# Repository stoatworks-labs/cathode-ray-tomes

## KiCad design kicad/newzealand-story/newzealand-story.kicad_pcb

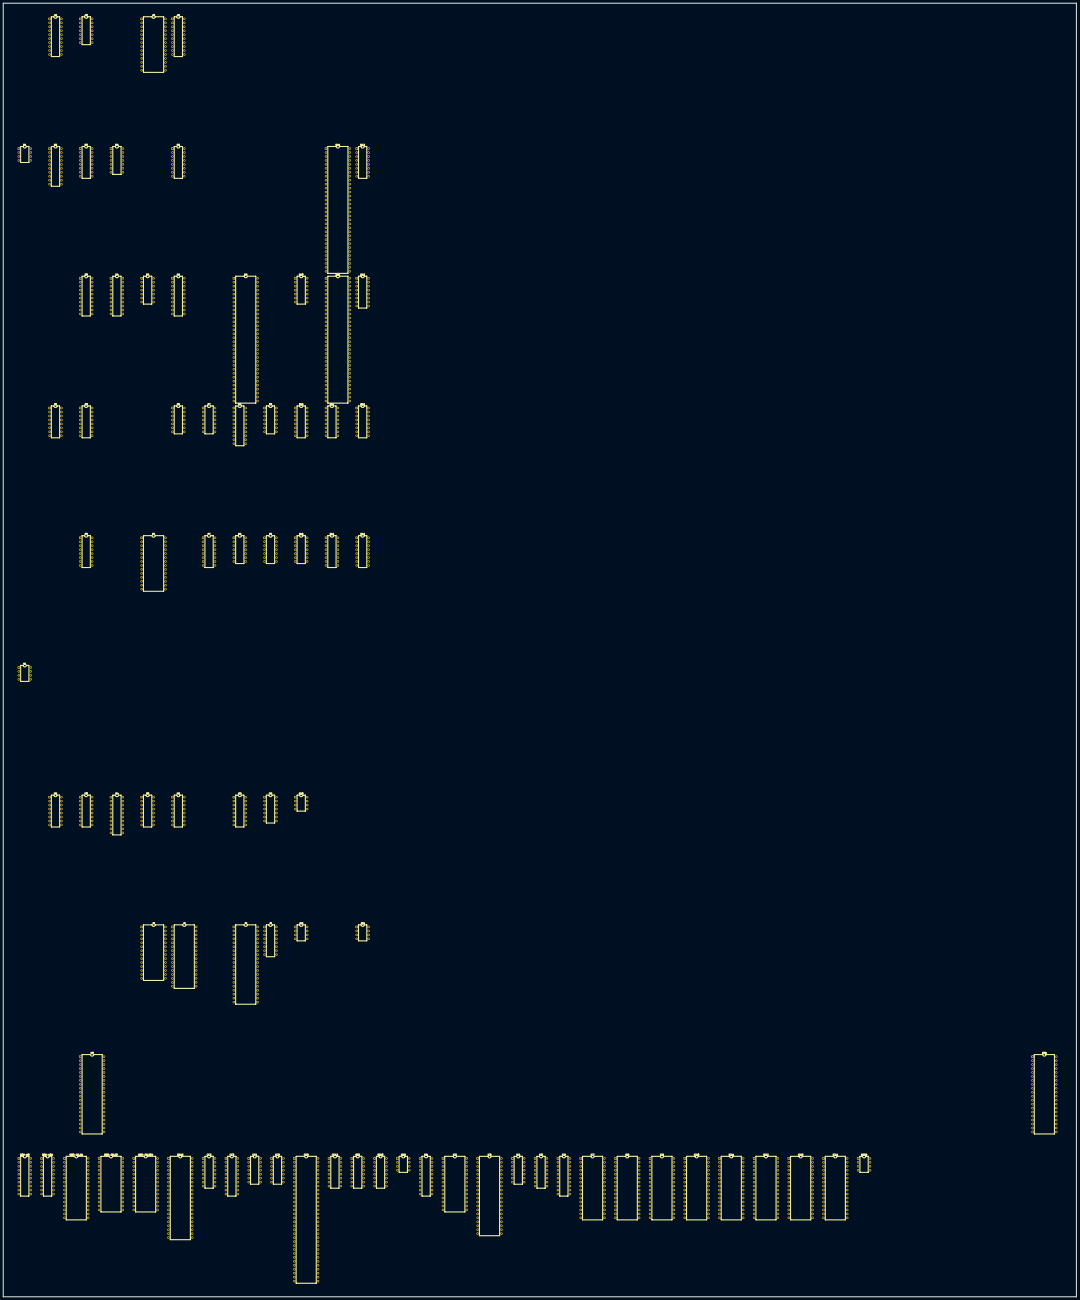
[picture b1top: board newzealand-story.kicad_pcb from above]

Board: 2 copper layers, 688.3 x 829.6 mm, 83 parts (0 on the bottom side), 406 nets, no tracks yet.

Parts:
A2: 74HC245; DIP-20_W7.62mm
A3: 74LS107; DIP-14_W7.62mm
A5: 6264SL; DIP-28_W15.24mm
A6: 74HC273; DIP-20_W7.62mm
B1: R0-012; DIP-8_W7.62mm
B2: 74HC245; DIP-20_W7.62mm
B3: 74F157; DIP-16_W7.62mm
B4: 74F32; DIP-14_W7.62mm
B6: 74HC174; DIP-16_W7.62mm
B06-13, B06-101: PAL16L8’; DIP-20_W7.62mm
B11: X1-006; DIP-64_W15.24mm
B12: X2-004; DIP-16_W7.62mm
B53-24.U1: 27C010; DIP-32_W15.24mm
B53-25.U3, B53-26.U34: 27512; DIP-28_W15.24mm
BB12: X1-007; DIP-42_W15.24mm
CC2: 74HC174; DIP-16_W7.62mm
CC3: 74HC245; DIP-20_W7.62mm
CC4: 74LS32; DIP-14_W7.62mm
CC5: 74F08; DIP-14_W7.62mm
CC8: YM3909; DIP-64_W15.24mm
CC12: X2-004; DIP-16_W7.62mm
D3, D4: 74HC245; DIP-20_W7.62mm
D5: 74LS32; DIP-14_W7.62mm
D6: 74HC374; DIP-20_W7.62mm
D8: YM3906; DIP-64_W15.24mm
D10: 74LS04; DIP-14_W7.62mm
D11: X1-004; DIP-64_W15.24mm
D12: X2-004; DIP-16_W7.62mm
E2, E3: 74LS157; DIP-16_W7.62mm
E6: 74F04; DIP-14_W7.62mm
E7: 74LS08; DIP-14_W7.62mm
E8: 74LS244_Split; DIP-20_W7.62mm
E9: 74LS74; DIP-14_W7.62mm
E10: 74LS139; DIP-16_W7.62mm
E11: 4050; DIP-16_W7.62mm
E12: X2-004; DIP-16_W7.62mm
EE8: 74LS157; DIP-16_W7.62mm
EE10: 74HC161; DIP-16_W7.62mm
F3, F7: 74LS157; DIP-16_W7.62mm
F5: uPD4464; DIP-28_W15.24mm
F8: 74LS74; DIP-14_W7.62mm
F9: 74LS32; DIP-14_W7.62mm
F10: 74HC14; DIP-14_W7.62mm
F11: 74HC161; DIP-16_W7.62mm
F12: TD62064; DIP-16_W7.62mm
G1: R0-012; DIP-8_W7.62mm
H2, H3: 74HC257; DIP-16_W7.62mm
H4: 74HC374; DIP-20_W7.62mm
H5: 74HC174; DIP-16_W7.62mm
H6: 74LS139; DIP-16_W7.62mm
H8: 74LS253; DIP-16_W7.62mm
H9: 74LS20; DIP-14_W7.62mm
H10: RC4558; DIP-8_W7.62mm
HH9: YM3014; DIP-8_W7.62mm
IC1: 74F245; DIP-20_W7.62mm
IC2: SRM20256; DIP-28_W15.24mm
IC3: Z80CPU; DIP-40_W15.24mm
IC4: 74HC08; DIP-14_W7.62mm
IC5: 74LS174; DIP-16_W7.62mm
IC6: PAL16L8’; DIP-20_W7.62mm
IC7, IC8, IC9, IC10, IC11, IC12, IC13, IC14: 27C010; DIP-32_W15.24mm
J5: HM65256BLP-12; DIP-28_W15.24mm
J6: 27C010; DIP-32_W15.24mm
J8: YM2203; DIP-40_W15.24mm
J9: HA17408; DIP-16_W7.62mm
J10: RC4558; DIP-8_W7.62mm
J12: MB3730; DIP-8_W7.62mm
R999: R0-012; DIP-8_W7.62mm
U3, U34: Z80CPU; DIP-40_W15.24mm

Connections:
+5V: H10.8, J9.13, J10.8
+12V: E11.1, F12.1, F12.8, J12.7
-5V: H10.4, J9.3
/CPU/H2B: B4.10, E7.4, E8.14, E9.12
/CPU/H4B: A2.19, B2.19, D5.12, E7.5, E8.12
/CPU/MCK6M: E9.3, IC4.9
/CPU/SA0: B11.48, B11.56, B53-25.U3.10, D11.37, EE8.2, H2.1, H3.1, U3.30
/CPU/SA1: B11.49, B11.57, B53-25.U3.9, E3.14, E10.2, F9.12, U3.31
/CPU/SA2: B11.50, B11.58, B53-25.U3.8, E3.11, F9.9, U3.32
/CPU/SA3: B11.51, B11.59, B53-25.U3.7, E3.5, U3.33
/CPU/SA4: B11.52, B11.60, B53-25.U3.6, E3.2, U3.34
/CPU/SA5: B11.53, B11.61, B53-25.U3.5, F3.14, U3.35
/CPU/SA6: B11.54, B11.62, B53-25.U3.4, F3.11, U3.36
/CPU/SA7: B11.55, B11.63, B53-25.U3.3, F3.5, U3.37
/CPU/SA8: B53-25.U3.25, F3.2, U3.38
/CPU/SA9: B53-25.U3.24, E2.14, U3.39
/CPU/SA10: B53-25.U3.21, E2.11, U3.40
/CPU/SA11: B06-13.5, B53-25.U3.23, E2.5, U3.1
/CPU/SA12: B06-13.4, B53-25.U3.2, E2.2, U3.2
/CPU/SA13: B06-13.3, U3.3
/CPU/SA14: B06-13.2, U3.4
/CPU/SA15: B06-13.1, B53-25.U3.1, U3.5
/CPU/SBSWD0: B06-13.11, D11.28, H5.15
/CPU/SBSWD1: B06-13.9, D11.29, H5.12
/CPU/SBSWD3: D11.31, H5.7
/CPU/SHA0: EE8.4, F5.10
/CPU/SHA1: E3.12, F5.9
/CPU/SHA2: E3.9, F5.8
/CPU/SHA3: E3.7, F5.7
/CPU/SHA4: E3.4, F5.6
/CPU/SHA5: F3.12, F5.5
/CPU/SHA6: F3.9, F5.4
/CPU/SHA7: F3.7, F5.3
/CPU/SHA8: F3.4, F5.25
/CPU/SHA9: E2.12, F5.24
/CPU/SHA10: E2.9, F5.21
/CPU/SHA11: E2.7, F5.23
/CPU/SHA12: E2.4, F5.2
/CPU/SHD0: D3.11, D4.11, F5.11
/CPU/SHD1: D3.12, D4.12, F5.12
/CPU/SHD2: D3.13, D4.13, F5.13
/CPU/SHD3: D3.14, D4.14, F5.15
/CPU/SHD4: D3.15, D4.15, F5.16
/CPU/SHD5: D3.16, D4.16, F5.17
/CPU/SHD6: D3.17, D4.17, F5.18
/CPU/SHD7: D3.18, D4.18, F5.19
/CPU/SRA13: B06-13.18, B53-25.U3.26
/CPU/SRA14: B06-13.19, B53-25.U3.27
/CPU/~BGTRNSP: B06-101.14, CC8.2
/CPU/~BNKSW: B06-101.15, CC2.9, D10.13
/CPU/~DIPSND: B06-13.15, F9.10, F9.13
/CPU/~H4: D6.1, E6.8, E7.2
/CPU/~MRD: CC3.1, D3.1, D8.2, E6.1, EE8.6, IC1.1, IC2.22, IC3.21, IC6.9
/CPU/~MRFSH: B06-101.9, E10.14, IC3.28
/CPU/~MSHRAMEN: CC4.6, CC5.13, D3.19, D5.10, E6.11
/CPU/~MSHRAMRQ: B06-101.18, CC4.2, CC4.4
/CPU/~MWR: B06-101.11, D5.9, IC2.27, IC3.22, IC6.8
/CPU/~OBJORVRAMEN: B06-101.19, CC4.13, D5.2, D5.13
/CPU/~OBJRAMCS: A5.20, E7.3
/CPU/~OE: EE8.7, F5.22
/CPU/~PALEN: B06-13.17, B11.45
/CPU/~RDINPUTS: B06-13.16, E10.1
/CPU/~SBNKSW: B06-13.14, H5.9
/CPU/~SMREQ: B06-13.7, U3.19
/CPU/~SRD: B11.44, D4.1, EE8.5, U3.21
/CPU/~SRFSH: B06-13.8, U3.28
/CPU/~SROMCS: B06-13.12, B53-25.U3.22
/CPU/~SRST: CC2.5, H5.1, J8.24, U3.26, U34.26
/CPU/~SSHRAMEN: CC4.1, CC4.8, CC4.12, CC5.12, D4.19, E2.1, E3.1, E6.13, EE8.1, F3.1
/CPU/~SSHRAMRQ: B06-13.13, CC4.10, D5.5
/CPU/~SWAIT: D5.6, U3.24
/CPU/~SWR: B06-13.6, B11.47, U3.22
/CPU/~VRAMWR: B06-101.13, D8.3
/Graphics/12M: CC8.3, D8.62
/Graphics/B1: B1.2, BB12.1
/Graphics/B2: B1.3, BB12.2
/Graphics/B3: B1.4, BB12.3
/Graphics/B4: B1.5, BB12.4
/Graphics/B5: B1.6, BB12.5
/Graphics/B6: B1.7, BB12.6
/Graphics/G1: BB12.7, G1.2
/Graphics/G2: BB12.8, G1.3
/Graphics/G3: BB12.9, G1.4
/Graphics/G4: BB12.11, G1.5
/Graphics/G5: BB12.12, G1.6
/Graphics/G6: BB12.13, G1.7
/Graphics/GA0: D8.35, IC7.12, IC8.12, IC9.12, IC10.12, IC11.12, IC12.12, IC13.12, IC14.12
/Graphics/GA1: D8.36, IC7.11, IC8.11, IC9.11, IC10.11, IC11.11, IC12.11, IC13.11, IC14.11
/Graphics/GA2: D8.37, IC7.10, IC8.10, IC9.10, IC10.10, IC11.10, IC12.10, IC13.10, IC14.10
/Graphics/GA4: D8.38, IC7.8, IC8.8, IC9.8, IC10.8, IC11.8, IC12.8, IC13.8, IC14.8
/Graphics/GA5: A6.19, IC7.7, IC8.7, IC9.7, IC10.7, IC11.7, IC12.7, IC13.7, IC14.7
/Graphics/GA6: A6.16, IC7.6, IC8.6, IC9.6, IC10.6, IC11.6, IC12.6, IC13.6, IC14.6
/Graphics/GA7: A6.15, IC7.5, IC8.5, IC9.5, IC10.5, IC11.5, IC12.5, IC13.5, IC14.5
/Graphics/GA8: A6.12, IC7.27, IC8.27, IC9.27, IC10.27, IC11.27, IC12.27, IC13.27, IC14.27
/Graphics/GA9: A6.9, IC7.26, IC8.26, IC9.26, IC10.26, IC11.26, IC12.26, IC13.26, IC14.26
/Graphics/GA10: A6.6, IC7.23, IC8.23, IC9.23, IC10.23, IC11.23, IC12.23, IC13.23, IC14.23
/Graphics/GA11: A6.5, IC7.25, IC8.25, IC9.25, IC10.25, IC11.25, IC12.25, IC13.25, IC14.25
/Graphics/GA12: A6.2, IC7.4, IC8.4, IC9.4, IC10.4, IC11.4, IC12.4, IC13.4, IC14.4
/Graphics/GA13: B6.15, IC7.28, IC8.28, IC9.28, IC10.28, IC11.28, IC12.28, IC13.28, IC14.28
/Graphics/GA14: B6.12, IC7.29, IC8.29, IC9.29, IC10.29, IC11.29, IC12.29, IC13.29, IC14.29
/Graphics/GA15: B6.10, IC7.3, IC8.3, IC9.3, IC10.3, IC11.3, IC12.3, IC13.3, IC14.3
/Graphics/GA16: B6.7, IC7.2, IC8.2, IC9.2, IC10.2, IC11.2, IC12.2, IC13.2, IC14.2
/Graphics/GDA0: CC8.56, IC7.13, IC8.13
/Graphics/GDA1: CC8.57, IC7.14, IC8.14
/Graphics/GDA2: CC8.58, IC7.15, IC8.15
/Graphics/GDA3: CC8.59, IC7.17, IC8.17
/Graphics/GDA4: CC8.60, IC7.18, IC8.18
/Graphics/GDA5: CC8.61, IC7.19, IC8.19
/Graphics/GDA6: CC8.62, IC7.20, IC8.20
/Graphics/GDA7: CC8.63, IC7.21, IC8.21
/Graphics/GDB0: CC8.48, IC9.13, IC10.13
/Graphics/GDB1: CC8.49, IC9.14, IC10.14
/Graphics/GDB2: CC8.50, IC9.15, IC10.15
/Graphics/GDB3: CC8.51, IC9.17, IC10.17
/Graphics/GDB4: CC8.52, IC9.18, IC10.18
/Graphics/GDB5: CC8.53, IC9.19, IC10.19
/Graphics/GDB6: CC8.54, IC9.20, IC10.20
/Graphics/GDB7: CC8.55, IC9.21, IC10.21
/Graphics/GDC0: CC8.40, IC11.13, IC13.13
/Graphics/GDC1: CC8.41, IC11.14, IC13.14
/Graphics/GDC2: CC8.42, IC11.15, IC13.15
/Graphics/GDC3: CC8.43, IC11.17, IC13.17
/Graphics/GDC4: CC8.44, IC11.18, IC13.18
/Graphics/GDC5: CC8.45, IC11.19, IC13.19
/Graphics/GDC6: CC8.46, IC11.20, IC13.20
/Graphics/GDC7: CC8.47, IC11.21, IC13.21
/Graphics/GDD0: CC8.30, IC12.13, IC14.13
/Graphics/GDD1: CC8.31, IC12.14, IC14.14
/Graphics/GDD2: CC8.34, IC12.15, IC14.15
/Graphics/GDD3: CC8.35, IC12.17, IC14.17
/Graphics/GDD4: CC8.36, IC12.18, IC14.18
/Graphics/GDD5: CC8.37, IC12.19, IC14.19
/Graphics/GDD6: CC8.38, IC12.20, IC14.20
/Graphics/GDD7: CC8.39, IC12.21, IC14.21
/Graphics/H: D8.40, E8.4
/Graphics/H2: D8.41, E8.6
/Graphics/H2SYNC: B4.8, D6.11, E6.3
/Graphics/H4: D8.42, E6.9, E8.8, H8.14
/Graphics/H8: A6.11, B6.9, D8.43, EE10.2
/Graphics/H8R: D8.34, IC7.9, IC8.9, IC9.9, IC10.9, IC11.9, IC12.9, IC13.9, IC14.9
/Graphics/HX: D8.39, E8.2
/Graphics/MAB11: B2.16, D8.27
/Graphics/OBJRD: B4.13, D8.30
/Graphics/R1: BB12.14, R999.2
/Graphics/R2: BB12.15, R999.3
/Graphics/R3: BB12.16, R999.4
/Graphics/R4: BB12.17, R999.5
/Graphics/R5: BB12.18, R999.6
/Graphics/R6: BB12.19, R999.7
/Graphics/VA0: A2.13, A5.10, D8.15
/Graphics/VA1: A2.14, A5.9, D8.16
/Graphics/VA2: A2.15, A5.8, D8.17
/Graphics/VA3: A2.16, A5.7, D8.18
/Graphics/VA4: A2.17, A5.6, D8.19
/Graphics/VA5: A2.18, A5.5, D8.20
/Graphics/VA6: A5.4, B2.11, D8.21
/Graphics/VA7: A5.3, B2.12, D8.22
/Graphics/VA8: A5.25, B2.13, D8.23
/Graphics/VA9: A5.24, B2.14, D8.24
/Graphics/VA10: A5.21, B2.15, D8.25
/Graphics/VA11: A5.23, D8.28
/Graphics/VA12: A5.2, H8.7
/Graphics/VD0: A5.11, A6.18, CC3.11, D6.18, D8.14
/Graphics/VD1: A5.12, A6.17, CC3.12, D6.17, D8.13
/Graphics/VD2: A5.13, A6.14, CC3.13, D6.14, D8.12
/Graphics/VD3: A5.15, A6.13, CC3.14, D6.13, D8.11
/Graphics/VD4: A5.16, A6.8, CC3.15, D6.8, D8.10
/Graphics/VD5: A5.17, A6.7, CC3.16, D6.7, D8.9
/Graphics/VD6: A5.18, A6.4, B2.3, CC3.17, D6.4, D8.8
/Graphics/VD7: A5.19, A6.3, B2.2, CC3.18, D6.3, D8.7
/Graphics/VDB0: B6.14, D6.19, D8.4
/Graphics/VDB1: B6.13, D6.16
/Graphics/VDB2: A2.12, B6.11, CC8.10, D6.15
/Graphics/VDB3: B6.6, CC8.9, D6.12
/Graphics/VDB4: B6.4, CC8.8, D6.9
/Graphics/VDB5: B6.3, CC8.7, D6.6
/Graphics/VDB6: B2.17, CC8.6, D6.5, D8.59
/Graphics/VDB7: B2.18, CC8.5, D6.2, D8.60
/Graphics/~GROMEN: B6.5, IC6.7, IC7.24, IC9.24, IC11.24, IC12.24
/Graphics/~HBLK2: D8.57, D10.9
/Graphics/~HBLK: D8.55, F10.1
/Graphics/~VBLK: A3.9, A3.12, BB12.24, D8.58
/Graphics/~VSYNC: BB12.23, D8.56
/IO/1P_BTN_1_B: D11.5, E12.12
/IO/1P_BTN_2_B: D11.4, E12.13
/IO/1P_BTN_3_B: D11.3, E12.14
/IO/1P_DOWN_B: D11.6, E12.11
/IO/1P_LEFT_B: D11.9, D12.14
/IO/1P_RIGHT_B: D11.8, D12.15
/IO/1P_START_B: D11.2, E12.15
/IO/1P_UP_B: D11.7, E12.10
/IO/2P_BTN_1_B: D11.13, D12.10
/IO/2P_BTN_2_B: D11.12, D12.11
/IO/2P_BTN_3_B: D11.11, D12.12
/IO/2P_DOWN_B: CC12.15, D11.14
/IO/2P_LEFT_B: CC12.12, D11.17
/IO/2P_RIGHT_B: CC12.13, D11.16
/IO/2P_START_B: D11.10, D12.13
/IO/2P_UP_B: CC12.14, D11.15
/IO/COIN_1_B: B12.14, D11.21
/IO/COIN_2_B: B12.15, D11.20
/IO/COIN_CNT_1_B: D11.25, F12.11
/IO/COIN_CNT_2_B: D11.24, F12.6
/IO/COIN_LOCK_1_B: D11.22, F12.14
/IO/COIN_LOCK_2_B: D11.23, F12.3
/IO/SD0: B53-25.U3.11, D4.9, D11.34, D11.44, H3.4, H4.18, H5.14, U3.14
/IO/SD1: B53-25.U3.12, D4.8, D11.35, D11.45, H3.7, H4.17, H5.13, U3.15
/IO/SD2: B53-25.U3.13, D4.7, D11.46, H3.9, H4.14, H5.11, U3.12
/IO/SD3: B53-25.U3.15, D4.6, D11.47, H3.12, H4.13, H5.6, U3.8
/IO/SD4: B53-25.U3.16, D4.5, D11.32, D11.48, H2.4, H4.8, H5.4, U3.7
/IO/SD5: B53-25.U3.17, D4.4, D11.33, D11.49, H2.7, H4.7, H5.3, U3.9
/IO/SD6: B53-25.U3.18, D4.3, D11.50, H2.9, H4.4, U3.10
/IO/SD7: B53-25.U3.19, D4.2, D11.51, H2.12, H4.3, U3.13
/IO/SERVICE_B: CC12.10, D11.19
/IO/TILT_B: CC12.11, D11.18
/Misc/HB: E8.3, F8.11
/Sound/DA0: J8.26, J9.12
/Sound/DA1: J8.27, J9.11
/Sound/DA2: J8.28, J9.10
/Sound/DA3: J8.29, J9.9
/Sound/DA4: J8.30, J9.8
/Sound/DA5: J8.31, J9.7
/Sound/DA6: J8.32, J9.6
/Sound/DA7: J8.33, J9.5
/Sound/ROMA14: B53-26.U34.27, F7.12, J6.29
/Sound/ROMA15: B53-26.U34.1, F7.7, J6.3
/Sound/S2A0: B53-26.U34.10, J5.10, J6.12, J8.37, U34.30
/Sound/S2A1: B53-26.U34.9, H6.14, J5.9, J6.11, U34.31
/Sound/S2A2: B53-26.U34.8, J5.8, J6.10, U34.32
/Sound/S2A3: B53-26.U34.7, J5.7, J6.9, U34.33
/Sound/S2A4: B53-26.U34.6, J5.6, J6.8, U34.34
/Sound/S2A5: B53-26.U34.5, J5.5, J6.7, U34.35
/Sound/S2A6: B53-26.U34.4, J5.4, J6.6, U34.36
/Sound/S2A7: B53-26.U34.3, J5.3, J6.5, U34.37
/Sound/S2A8: B53-26.U34.25, J5.25, J6.27, U34.38
/Sound/S2A9: B53-26.U34.24, J5.24, J6.26, U34.39
/Sound/S2A10: B53-26.U34.21, J5.21, J6.23, U34.40
/Sound/S2A11: B53-26.U34.23, J5.23, J6.25, U34.1
/Sound/S2A12: B53-26.U34.2, J5.2, J6.4, U34.2
/Sound/S2A13: B53-26.U34.26, J6.28, U34.3
/Sound/S2A14: F7.14, H6.2, U34.4
/Sound/S2A15: F7.1, H6.3, U34.5
/Sound/S2D0: B53-26.U34.11, H4.19, J5.11, J6.13, J8.40, U34.14
/Sound/S2D1: B53-26.U34.12, H4.16, J5.12, J6.14, J8.2, U34.15
/Sound/S2D2: B53-26.U34.13, H4.15, J5.13, J6.15, J8.3, U34.12
/Sound/S2D3: B53-26.U34.15, H4.12, J5.15, J6.17, J8.4, U34.8
/Sound/S2D4: B53-26.U34.16, H4.9, J5.16, J6.18, J8.5, U34.7
/Sound/S2D5: B53-26.U34.17, H4.6, J5.17, J6.19, J8.6, U34.9
/Sound/S2D6: B53-26.U34.18, H4.5, J5.18, J6.20, J8.7, U34.10
/Sound/S2D7: B53-26.U34.19, H4.2, J5.19, J6.21, J8.8, U34.13
/Sound/YMROMA14: F7.13, J8.16
/Sound/YMROMA15: F7.6, J8.15
/Sound/~ROMCS2: B53-26.U34.20, J6.22
/Sound/~ROMOE2: B53-26.U34.22, J6.24
/Sound/~S2INT: F8.6, U34.16
/Sound/~S2IORQ: H6.15, U34.20
/Sound/~S2M1: D10.11, H6.13, U34.27
/Sound/~S2MREQ: F7.11, H6.1, U34.19
/Sound/~S2RAMCS: H6.7, J5.20
/Sound/~S2RD: J5.22, J8.36, U34.21
/Sound/~S2ROMHCS: F7.10, H6.6
/Sound/~S2WR: J5.27, J8.35, U34.22
/Sound/~YMCS: H6.10, J8.34
/Sound/~YMIRQ: J8.25, U34.17
/Sound/~YMROMOE: F7.3, J8.14
/Sub PCB/MA0: A2.7, B53-24.U1.12, CC3.9, EE8.3, IC2.10, IC3.30
/Sub PCB/MA1: A2.6, B53-24.U1.11, CC3.8, E3.13, IC2.9, IC3.31
/Sub PCB/MA2: A2.5, B53-24.U1.10, CC3.7, E3.10, IC2.8, IC3.32
/Sub PCB/MA3: A2.4, B53-24.U1.9, CC3.6, E3.6, IC2.7, IC3.33
/Sub PCB/MA4: A2.3, B53-24.U1.8, CC3.5, E3.3, IC2.6, IC3.34
/Sub PCB/MA5: A2.2, B53-24.U1.7, CC3.4, F3.13, IC2.5, IC3.35
/Sub PCB/MA6: B2.9, B53-24.U1.6, CC3.3, F3.10, IC2.4, IC3.36
/Sub PCB/MA7: B2.8, B53-24.U1.5, CC3.2, F3.6, IC2.3, IC3.37
/Sub PCB/MA8: B2.7, B53-24.U1.27, F3.3, IC2.25, IC3.38
/Sub PCB/MA9: B2.6, B06-101.7, B53-24.U1.26, E2.13, IC2.24, IC3.39, IC6.18
/Sub PCB/MA10: B2.5, B06-101.6, B53-24.U1.23, E2.10, IC2.21, IC3.40, IC6.1
/Sub PCB/MA11: B2.4, B06-101.5, B53-24.U1.25, D8.26, E2.6, IC2.23, IC3.1, IC6.2
/Sub PCB/MA12: B06-101.4, B53-24.U1.4, E2.3, IC2.2, IC3.2, IC6.3
/Sub PCB/MA13: B06-101.3, B53-24.U1.28, D10.1, IC2.26, IC3.3, IC6.4
/Sub PCB/MA14: B3.10, B4.2, B06-101.2, H9.2, IC3.4, IC6.5
/Sub PCB/MA15: B06-101.1, CC5.2, D10.5, H9.1, IC3.5, IC6.6
/Sub PCB/MBD0: B53-24.U1.13, CC2.14, D3.9, IC1.18
/Sub PCB/MBD1: B53-24.U1.14, CC2.13, D3.8, IC1.17
/Sub PCB/MBD2: B53-24.U1.15, CC2.11, D3.7, IC1.16
/Sub PCB/MBD3: B53-24.U1.17, CC2.6, D3.6, IC1.15
/Sub PCB/MBD4: B53-24.U1.18, CC2.4, D3.5, IC1.14
/Sub PCB/MBD5: B53-24.U1.19, CC2.3, D3.4, IC1.13
/Sub PCB/MBD6: B53-24.U1.20, D3.3, IC1.12
/Sub PCB/MBD7: B53-24.U1.21, D3.2, IC1.11
/Sub PCB/MD0: IC1.2, IC2.11, IC3.14, IC5.3
/Sub PCB/MD1: IC1.3, IC2.12, IC3.15, IC5.4
/Sub PCB/MD2: IC1.4, IC2.13, IC3.12, IC5.6
/Sub PCB/MD3: IC1.5, IC2.15, IC3.8, IC5.11
/Sub PCB/MD4: IC1.6, IC2.16, IC3.7, IC5.13
/Sub PCB/MD5: IC1.7, IC2.17, IC3.9, IC5.14
/Sub PCB/MD6: IC1.8, IC2.18, IC3.10
/Sub PCB/MD7: IC1.9, IC2.19, IC3.13
/Sub PCB/MDC0: IC2.1, IC5.2, IC6.17
/Sub PCB/MDC1: IC5.5, IC6.16
/Sub PCB/MDC2: IC5.7, IC6.15
/Sub PCB/~GROMENB: IC6.14, IC8.24, IC10.24, IC13.24, IC14.24
/Sub PCB/~MINT: A3.6, IC3.16
/Sub PCB/~MIORQ: A3.10, IC3.20
/Sub PCB/~MMREQ: B4.4, B06-101.8, E10.13, IC3.19, IC6.11
/Sub PCB/~MRAMCS: IC2.20, IC6.12
/Sub PCB/~MWAIT: CC5.6, IC3.24
/Sub PCB/~WDRES: CC2.1, D8.29, F10.10, IC3.26
GND: A2.8, A2.9, A3.4, A3.11, A5.22, B1.8, B3.3, B3.6, B3.15, B06-13.10, B06-101.10, B11.19, B11.20, B11.21, B11.22, B11.33, B11.46, B12.9, B12.16, B53-24.U1.16, B53-24.U1.22, B53-25.U3.14, B53-25.U3.20, B53-26.U34.14, BB12.21, BB12.26, CC8.32, CC8.64, CC12.9, CC12.16, D8.31, D8.32, D8.45, D8.64, D11.1, D11.26, D11.36, D11.38, D11.39, D11.43, D12.9, D12.16, E2.15, E3.15, E7.9, E7.10, E7.12, E7.13, E8.1, E8.19, E10.3, E10.15, E11.8, E12.9, E12.16, EE8.10, EE8.11, EE8.13, EE8.14, EE8.15, F3.15, F7.2, F7.5, F7.15, F11.3, F11.4, F11.5, F11.6, F12.4, F12.5, F12.12, F12.13, G1.8, H8.1, H8.2, H8.8, H10.3, H10.5, HH9.6, IC2.14, IC3.29, IC4.1, IC4.2, IC4.4, IC4.5, IC4.12, IC4.13, IC6.10, IC7.16, IC7.22, IC8.16, IC8.22, IC9.16, IC9.22, IC10.16, IC10.22, IC11.16, IC11.22, IC12.16, IC12.22, IC13.16, IC13.22, IC14.16, IC14.22, J6.16, J8.1, J9.2, J10.4, J12.4, R999.8, U3.29, U34.29
unnamed: A3.2, U3.16
unnamed: A3.13, U3.20
unnamed: A5.27, B4.11
unnamed: B3.2, CC2.10
unnamed: B3.5, CC2.12
unnamed: B3.11, CC2.15
unnamed: B3.1, B4.3, CC5.1
unnamed: B3.7, B53-24.U1.3
unnamed: B3.9, B53-24.U1.29
unnamed: B4.1, D10.6
unnamed: B4.5, CC5.3
unnamed: B4.12, E6.2
unnamed: B11.23, CC8.20
unnamed: B11.24, CC8.21
unnamed: B11.25, CC8.22
unnamed: B11.26, CC8.23
unnamed: B11.27, CC8.24
unnamed: B11.28, CC8.25
unnamed: B11.29, CC8.26
unnamed: B11.30, CC8.27
unnamed: B11.31, CC8.28
unnamed: B11.1, BB12.41
unnamed: B11.2, BB12.40
unnamed: B11.3, BB12.39
unnamed: B11.4, BB12.38
unnamed: B11.5, BB12.37
unnamed: B11.6, BB12.36
unnamed: B11.7, BB12.35
unnamed: B11.8, BB12.34
unnamed: B11.9, BB12.33
unnamed: B11.10, BB12.32
unnamed: B11.11, BB12.31
unnamed: B11.12, BB12.30
unnamed: B11.13, BB12.29
unnamed: B11.14, BB12.28
unnamed: B11.15, BB12.27
unnamed: BB12.22, EE10.12
unnamed: E11.2, E11.4, E11.6, E11.10, E11.12
unnamed: CC3.19, D5.11
unnamed: CC4.3, CC5.5
unnamed: CC4.5, D5.4, E6.12
unnamed: CC4.9, E6.10
unnamed: CC4.11, CC5.10
unnamed: CC5.4, D5.3
unnamed: CC5.9, D5.8
unnamed: CC8.4, D8.61
unnamed: CC8.19, D8.46
unnamed: CC8.18, D8.47
unnamed: CC8.17, D8.48
unnamed: CC8.16, D8.49
unnamed: CC8.15, D8.50
unnamed: CC8.14, D8.51
unnamed: CC8.13, D8.52
unnamed: CC8.12, D8.53
unnamed: CC8.11, D8.54
unnamed: D10.2, H9.4
unnamed: D10.12, F9.5
unnamed: D11.40, E10.5
unnamed: D11.41, E10.4
unnamed: E7.1, H9.6
unnamed: E8.17, E8.18
unnamed: E7.6, E9.2
unnamed: D5.1, E9.5
unnamed: E8.11, E8.13, E8.16, E9.11
unnamed: B4.9, E9.8
unnamed: E10.11, H9.13
unnamed: E11.3, E11.5, E11.7, E11.9, E11.11, E11.15
unnamed: EE10.9, F10.2
unnamed: CC5.11, F5.20
unnamed: CC5.8, F5.27
unnamed: F8.3, F9.11, H4.11
unnamed: F8.1, H4.1, H6.9
unnamed: F8.8, F8.12
unnamed: F8.9, U34.24
unnamed: D10.10, F8.10
unnamed: F10.4, F10.5
unnamed: F9.6, F10.9
unnamed: F9.3, F10.11
unnamed: F9.2, F9.4, F10.12
unnamed: F10.6, F11.2
unnamed: F9.1, F11.11
unnamed: F10.8, F11.1
unnamed: F9.8, H2.15, H3.15
unnamed: E6.4, H8.5
unnamed: H9.5, H9.8
unnamed: H10.6, J9.4
unnamed: HH9.2, J10.3
unnamed: HH9.3, J8.22
unnamed: HH9.8, J10.6, J10.7
unnamed: HH9.5, J8.39
unnamed: HH9.7, J10.5
unnamed: HH9.4, J8.23
unnamed: IC1.19, IC6.13
unnamed: IC3.6, IC4.8
unnamed: IC5.9, IC6.19
unnamed: J8.18, J8.19, J8.20
unnamed: J10.1, J10.2
VCC: A2.1, A3.1, A3.8, A5.26, A6.1, B2.1, B6.1, B06-13.20, B06-101.20, B11.17, B11.18, B11.64, B12.1, B12.8, B53-24.U1.1, B53-24.U1.31, B53-24.U1.32, B53-25.U3.28, B53-26.U34.28, BB12.42, CC8.1, CC8.33, CC12.1, CC12.8, D8.1, D8.33, D11.27, D11.42, D11.52, D12.1, D12.8, E9.1, E9.4, E9.10, E9.13, E12.1, E12.8, EE10.1, EE10.3, EE10.4, EE10.5, EE10.6, EE10.7, EE10.10, F5.26, F8.2, F8.4, F8.13, F11.7, F11.10, H8.16, H9.9, H9.10, H9.12, HH9.1, IC2.28, IC3.11, IC3.17, IC4.10, IC5.1, IC6.20, IC7.1, IC7.31, IC7.32, IC8.1, IC8.31, IC8.32, IC9.1, IC9.31, IC9.32, IC10.1, IC10.31, IC10.32, IC11.1, IC11.31, IC11.32, IC12.1, IC12.31, IC12.32, IC13.1, IC13.31, IC13.32, IC14.1, IC14.31, IC14.32, J5.26, J6.1, J6.31, J6.32, J8.21, U3.11, U3.17, U3.25, U34.11, U34.25
